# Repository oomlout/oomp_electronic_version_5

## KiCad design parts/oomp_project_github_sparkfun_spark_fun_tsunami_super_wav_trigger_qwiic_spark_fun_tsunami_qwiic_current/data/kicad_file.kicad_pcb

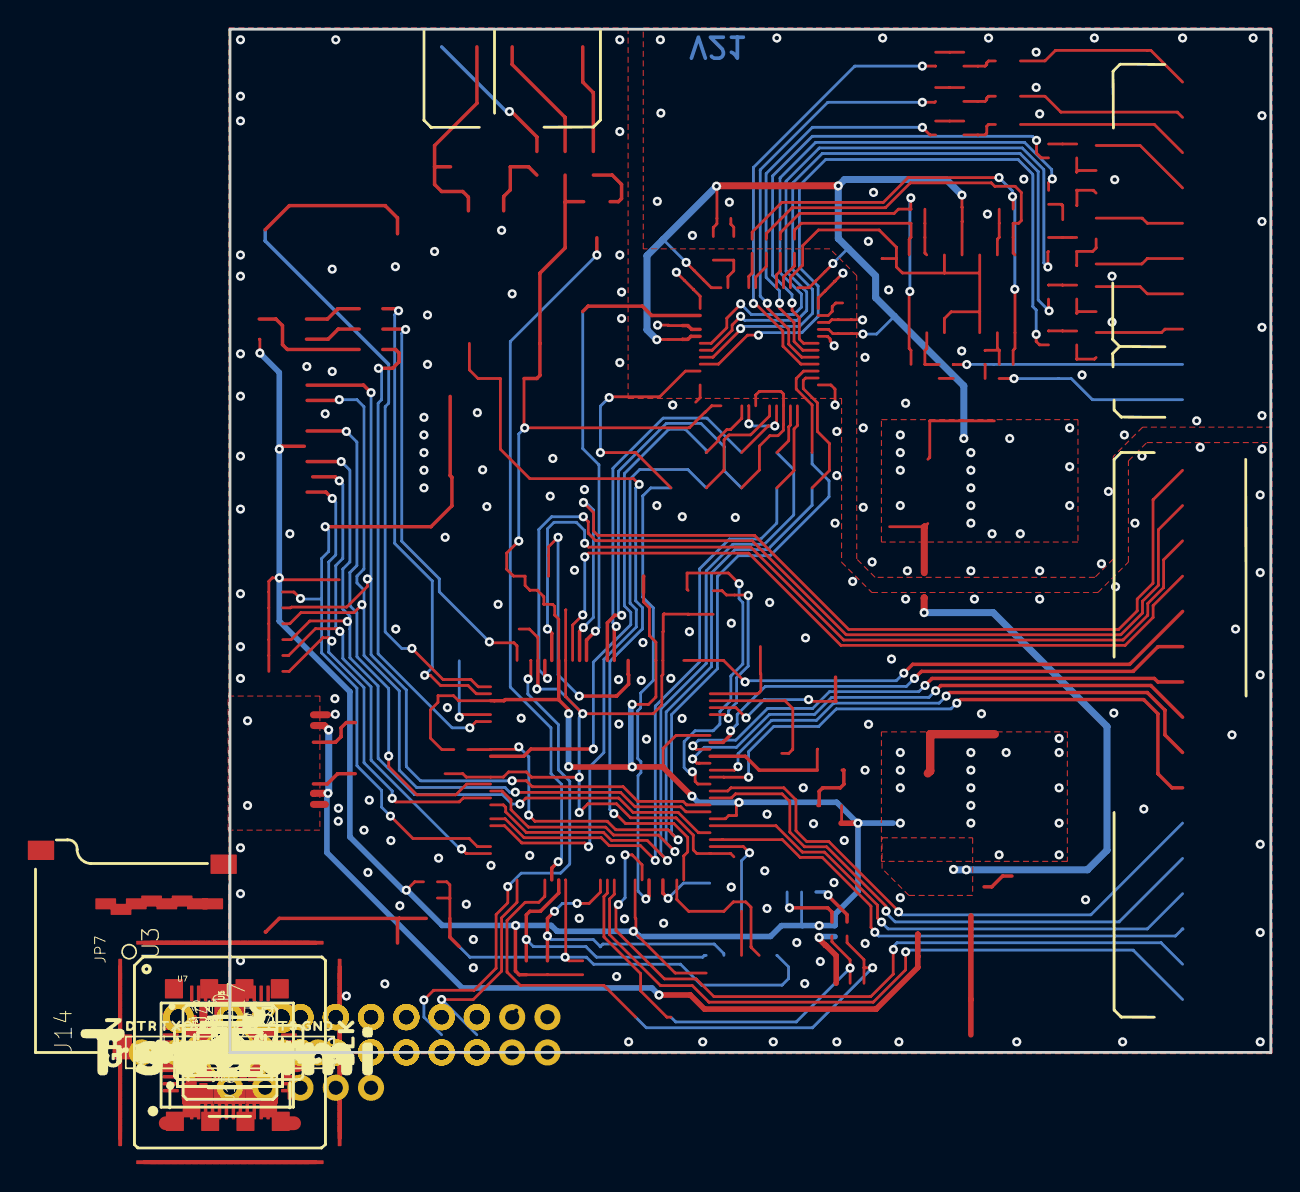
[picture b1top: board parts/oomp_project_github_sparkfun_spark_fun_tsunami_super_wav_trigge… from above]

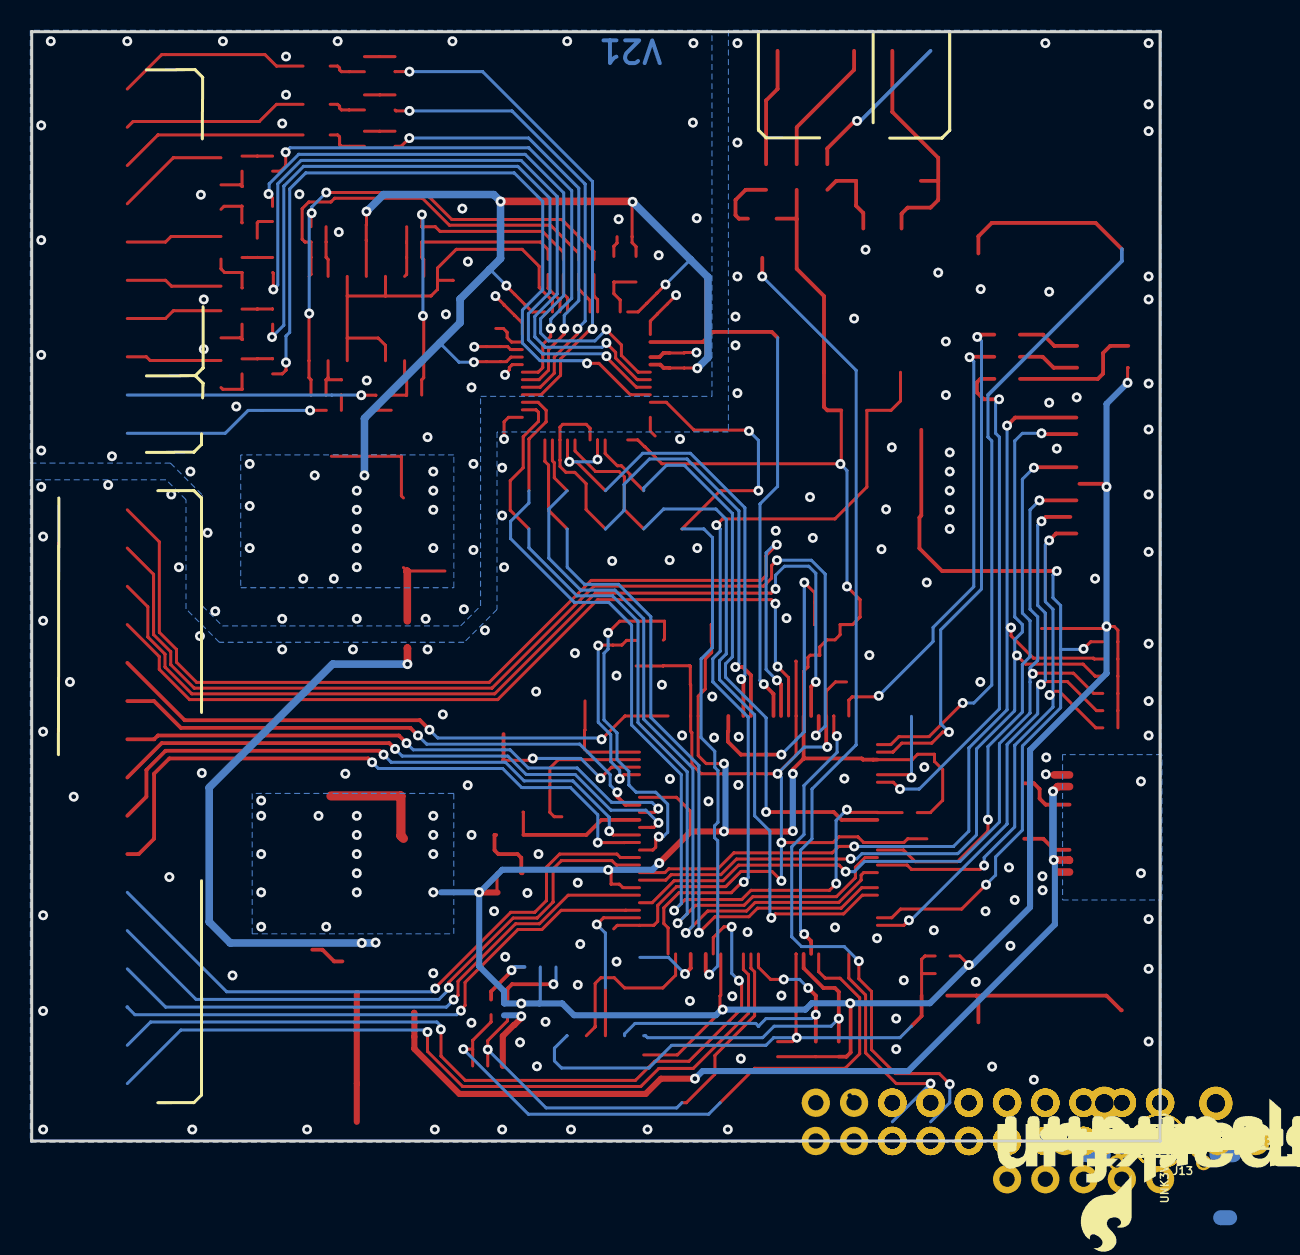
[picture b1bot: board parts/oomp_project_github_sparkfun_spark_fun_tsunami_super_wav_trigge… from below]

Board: 2 copper layers, 74.9 x 73.7 mm, 327 parts (76 on the bottom side), 138 nets.

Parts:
C1: 10nF; 0402-TIGHT
C2, C5, C6, C11, C27: 10uF; 0402-TIGHT
C3, C4, C8, C10, C12, C13, C15, C16, C17, C18, C19, C21, C22, C23, C24, C26, C28, C29, C31, C36, C37, C47, C48, C49, C50, C51, C52, C53, C54, C55, C56, C57, C59, C73, C74, C75, C76, C77, C78, C79, C80: 0.1uF; 0402-TIGHT
C7, C9: 12pF; 0402-TIGHT
C14: 4.7uF; 0402-TIGHT
C20: 10pF; 0603
C25: 2.2uF; 0603
C30, C32, C38, C58, C60, C62, C63, C66, C69, C70, C71, C72: 1.0uF; 0402-TIGHT
C33, C61, C67, C68: 100pF; 0402-TIGHT
C34: 5.6nF; 0603
C35: 390nF; 0603
C39, C40, C41, C42, C43, C44, C45, C46: 22uF; 0805
D1, D3: 1A/40V/500mV; SMA-DIODE
D4: RGB; P-LCC-4-3
FB1, FB2, FB3: 470Ω; 0603
FB4, FB5: 600Ω; 0805
FD1, FD2, FD3, FD4: FIDUCIALUFIDUCIAL; FIDUCIAL-MICRO
FRAME1, FRAME2: FRAME-LEDGER; CREATIVE_COMMONS
H1, H2, H3, H4: STAND-OFF
I2C0: SMT-JUMPER_3_2-NC_TRACE_SILK
J1: VDC-IN; 1X02_NO_SILK
J2: GND-IN; 1X02_NO_SILK
J3: DEBUG; 1X01_NO_SILK
J4: QWIIC; JST04_1MM_RA
J6: 3.3VA; 1X01_NO_SILK
J7: 3.3V; 1X01_NO_SILK
J8: PLAYING; 1X01_NO_SILK
J9: CORTEX_JTAG_DEBUG_PTH_NS; 2X5-PTH-1.27MM-NO_SILK
J10: TRIG2; 2X8_NOSILK
J11: TRIG1; 2X8_NOSILK
J13: 2X5_NOSILK
J14: AUDIO I/O; 2X10_NOSILK
J15: MIDI; 1X05_NO_SILK
J16: USB-C; USB-C-16P-4LAYER-ISOLATED
J17: AGND; 1X01_NO_SILK
J18: 6_PIN_SERIAL_TARGET_SIDE_W_SILK
JP7: USD-SOCKETNEW; MICRO-SD-SOCKET-PP
L1: 10μH; 0805
LOGO2: SFE_LOGO_NAME_FLAME.2_INCH; SFE_LOGO_NAME_FLAME_.2
LOGO3: QWIIC_LOGO_4MM; QWIIC_4MM
Q1: 3.1A/30V/105mΩ; SOT23-3
R1: 33; 0603
R2: 1M; 0603
R3, R4, R18, R23: 10k; 0402-TIGHT
R5: 560Ω; 0402-TIGHT
R6, R9, R10, R19, R20, R21, R22: 100k; 0402-TIGHT
R7, R8: 390; 0603
R11, R12: 240; 0603
R14, R15, R59, R60, R61, R62, R63, R64: 33k; 0402-TIGHT
R16: 2.2; 0603
R17: 5.62k; 0603
R25, R26, R27, R28, R37, R38, R39, R40, R41, R42, R43, R44, R56, R57, R58, R65: 10Ω; 0402-TIGHT
R45, R46, R47, R48, R55: 220; 0603
R49, R50: 5.1k; 0402-TIGHT
R51, R52: 2.2k; 0402-TIGHT
R53, R54: 100; 0603
S1: Reset; TACTILE_SWITCH_SMD_5.2MM
S2, S4: DNP; TACTILE_SWITCH_PTH_RIGHT_ANGLE
S3: User; TACTILE_SWITCH_SMD_5.2MM
TP1: I2C_SCK; TP_15TH
TP2: I2C_SDA; TP_15TH
TP4: MCLK; TP_15TH
TP5: SWDIO/TMS; TP_15TH
TP6: SWCK/TCK; TP_15TH
TP7: TDO; TP_15TH
TP8: TDI; TP_15TH
TP9: NRESET; TP_15TH
U1, U5: LM1117; SOT223
U3: ATSAMS70NXXA-AN; LQFP100
U4: LMV324; SO14
U6: 6N138M; 8-SMD
U7: ADAU1328; LQFP-48
U8: 74AHC1G125W5-7; SOT23-5
U$3: GND_0
U$4, U$73: QWIIC_5MM
U$5: STAT0
U$6: #USER#0
U$7: #RESET#0
U$8, U$9: ROBERTSONICS0
U$10, U$167: #2L#0
U$11: #1L#0
U$12, U$120: #1R#0
U$13: #2R#0
U$14: #3R#0
U$15: #3L#0
U$16: #4L#0
U$17: #4R#0
U$18: #4#3
U$19: #2#5
U$20, U$107: AUDIO_OUT0
U$21, U$46, U$108, U$123: IN0
U$22, U$106: TRIGGER_IN0
U$23, U$85: #GND#0
U$24: #1#0
U$25: SERIAL3
U$26, U$60: SUPER0
U$27, U$99: VIN_5#10_VDC0
U$28, U$84: #AGND#0
U$29: #2#0
U$30: #3#0
U$31, U$56, U$117: #4#0
U$32, U$58, U$118: #5#0
U$33: #6#0
U$34: #7#0
U$35: #8#0
U$36: #9#0
U$37: #10#0
U$38: #11#0
U$39: #12#0
U$40: #PLAYING#30
U$41, U$112: #3V3#0
U$43: #13#0
U$44: #3V3_A#0
U$45, U$122: MIDI0
U$47, U$124: OUT0
U$48: #14#0
U$49: #15#0
U$50: #16#0
U$51: A10
U$52: A20
U$53: A30
U$54: A40
U$55: #5#6
U$57: #2#6
U$59: #4#6
U$61, U$110: #GND#1
U$62, U$68: TRIGGER0
U$63, U$69: TSUNAMI0
U$64, U$70: W0
U$65, U$71: A0
U$66, U$72: V0
U$67, U$111: #VIN#2
U$74: #16#5
U$75: #15#17
U$76: #14#17
U$77: #13#17
U$78: #12#17
U$79: #11#17
U$80: #10#17
U$81: #9#17
U$82: #8#17
U$83: #7#17
U$86: CS17
U$87: BCLK19
U$88: COPI18
U$89: TDMO20
U$91: SPCK22
U$92: TDMI25
U$93: LRCK24
U$94: CIPO23
U$95: APDM26
U$96: #AGND#27
U$97: #AGND#28
U$98: #PLAYING#29
U$102: A117
U$103: A2118
U$104: A32119
U$105: A432120
U$113: #I2C#6
U$116: #1L#3
U$119: #1L#6
U$121: #1R#2
U$141: SFE_LOGO_NAME_FLAME_.1
U$162: #3V3_A#4
U$163: #3V3_QWIIC#0
U$164: #1R#3
U$165: #5#5
U$166: #1L#2
U$168: #2R#3
U$169: #3L#3
U$170: #3R#4
U$171: #4L#4
U$172: #4R#5
U$173: #6#17
U$174: #5#17
U$175: #4#17
U$176: #3#17
U$177: #2#17
U$178: #1#17
UNK3V3_QWIIC0: SMT-JUMPER_2_NO_SILK
Y1: 11.2896 MHz; CRYSTAL-OSC-SMD-5X3

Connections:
3.3V: C6.1, C8.1, C10.1, C11.1, C12.1, C13.1, C15.1, C16.1, C27.1, C28.1, C36.1, C62.1, D4.4, FB3.1, I2C0.2, J7.1, J9.1, JP7.VCC, R3.2, R4.2, R6.2, R9.2, R10.2, R12.2, R16.1, R18.2, R19.2, R20.2, R21.2, R22.2, R23.2, R47.2, R48.2, U1.2, U1.4, U3.5, U3.19, U3.28, U3.68, U3.81, U3.93, U6.8, U7.13, U8.5, UNK3V3_QWIIC0.1
56: D3.C, R45.2, U6.2
ADC1LN: C69.1, U7.40
ADC1LP: C70.1, U7.39
ADC2LN: C71.1, U7.44
ADC2LP: C72.1, U7.43
AGND: C3.2, C5.2, C29.2, C30.2, C31.2, C32.2, C37.2, C38.2, C47.2, C48.2, C49.2, C50.2, C51.2, C52.2, C53.2, C54.2, C55.2, C56.2, C57.2, C58.2, C59.2, C60.2, C73.1, C74.1, C75.1, C76.1, C77.1, C78.1, C79.1, C80.1, FB4.2, J14.2, J14.4, J14.6, J14.8, J14.10, J14.12, J14.14, J14.16, J14.18, J14.20, J17.1, R7.1, U4.11, U7.1, U7.4, U7.32, U7.34, U7.36
AIN1L: C63.2, J14.17
AIN1R: C66.2, J14.19
AOUT1L: C46.1, C47.1, R37.2
AOUT1R: C45.1, C48.1, R38.2
AOUT2L: C44.2, J14.5
AOUT2R: C43.1, C50.1, R40.2
AOUT3L: C42.2, J14.9
AOUT3R: C41.1, C52.1, R42.2
AOUT4L: C40.1, C53.1, R43.2
AOUT4R: C39.1, C54.1, R44.2
APDN: J13.9, U3.70, U7.10
BCLK: J13.6, U3.11, U7.17, U7.21
BLUE_LED: R54.1, U3.31
CC1: J16.A5, R50.2
CC2: J16.B5, R49.2
CM_1.5V: C55.1, U4.3, U4.5, U4.10, U4.12, U7.38
DBUG: J3.1, U3.72
DGND: C1.2, C2.2, C4.2, C6.2, C7.2, C8.2, C9.2, C10.2, C11.2, C12.2, C13.2, C14.2, C15.2, C16.2, C17.2, C18.2, C19.2, C20.2, C21.2, C22.2, C23.2, C24.2, C25.2, C26.2, C27.2, C28.2, C36.2, C62.2, FB4.1, J2.1, J2.2, J4.1, J9.3, J9.5, J9.9, J10.2, J10.4, J10.6, J10.8, J10.10, J10.12, J10.14, J10.16, J11.2, J11.4, J11.6, J11.8, J11.10, J11.12, J11.14, J11.16, J13.10, J15.4, J16.GND, J16.GND2, J18.6, JP7.GND, JP7.GND1, JP7.GND3, R2.1, R8.1, R17.1, R49.1, R50.1, S1.1, S2.1, S3.1, S4.1, U3.3, U3.6, U3.7, U3.8, U3.10, U3.29, U3.67, U6.5, U7.12, U7.25, U8.1, U8.3, Y1.2, Y1.4
GREEN_LED: R53.1, U3.27
I2C_SCK: J4.4, R52.1, TP1.1, U3.55
I2C_SDA: J4.3, R51.1, TP2.1, U3.64
LF: C34.1, C35.1, U7.47
LRCK: J13.5, U3.12, U7.18, U7.22
MCLK: TP4.1, U3.15, U7.2
MIDI-IN-PIN4: J15.1, R45.1
MIDI-IN-PIN5: D3.A, J15.2, U6.3
MIDI-OUT-PIN4: J15.3, R47.1
MIDI-OUT-PIN5: J15.5, R46.2
MIN: R48.1, U3.75, U6.6
MOUT: U3.56, U8.2
unnamed: C7.1, U3.98, Y1.1
unnamed: C9.1, U3.99, Y1.3
unnamed: C19.1, FB1.1, U3.96
unnamed: C14.1, L1.2, U3.90
unnamed: C23.1, FB2.1, U3.86
unnamed: C33.2, C69.2, R14.2, R60.1, U4.8
unnamed: I2C0.3, R51.2
unnamed: J8.1, U3.30
unnamed: I2C0.1, R52.2
unnamed: C34.2, R5.2
unnamed: C63.1, R15.1
unnamed: C61.2, C70.2, R59.2, U4.7
unnamed: C68.2, C72.2, R63.2, U4.1
unnamed: C20.1, R17.2, U3.97
unnamed: C26.1, FB3.2, U3.9
unnamed: C39.2, J14.15
unnamed: C40.2, J14.13
unnamed: C41.2, J14.11
unnamed: C42.1, C51.1, R41.2
unnamed: C43.2, J14.7
unnamed: C75.2, R25.2, R37.1
unnamed: L1.1, R16.2
unnamed: R7.2, R11.1, U5.1
unnamed: R1.1, S1.3, S2.2
unnamed: C74.2, R44.1, R65.2
unnamed: C73.2, R43.1, R58.2
unnamed: R8.2, R12.1, U1.1
unnamed: C80.2, R42.1, R57.2
unnamed: C44.1, C49.1, R39.2
unnamed: C46.2, J14.1
unnamed: C45.2, J14.3
unnamed: J4.2, UNK3V3_QWIIC0.2
unnamed: D4.2, R53.2
unnamed: D4.3, R54.2
unnamed: D4.1, R55.2
unnamed: R46.1, U8.4
unnamed: C3.1, FB5.2, U5.3
unnamed: C56.1, U7.35
unnamed: C61.1, R59.1, R60.2, U4.6
unnamed: C33.1, R14.1, R15.2, U4.9
unnamed: C79.2, R41.1, R56.2
unnamed: C78.2, R28.2, R40.1
unnamed: C76.2, R26.2, R38.1
unnamed: C77.2, R27.2, R39.1
unnamed: C67.2, C71.2, R61.2, R64.1, U4.14
unnamed: C66.1, R62.1
unnamed: C68.1, R63.1, R64.2, U4.2
unnamed: C67.1, R61.1, R62.2, U4.13
unnamed: Q1.1, R2.2
NRESET: C1.1, J9.10, R1.2, R3.1, R10.1, TP9.1, U3.58
OL1: R25.1, U7.28
OL2: R27.1, U7.30
OL3: R56.1, U7.6
OL4: R58.1, U7.8
OR1: R26.1, U7.29
OR2: R28.1, U7.31
OR3: R57.1, U7.7
OR4: R65.1, U7.9
RED_LED: R55.1, U3.25
REGINPUTS: C4.1, D1.C, FB5.1, Q1.2, U1.3
RXD: J18.3, U3.51
SDCD: JP7.CD1, JP7.CD2, R18.1, U3.49
SDCLK: JP7.SCLK, U3.40
SDCMD: JP7.DI, R23.1, U3.79
SDD0: JP7.DO, R21.1, U3.82
SDD1: JP7.RSV2, R22.1, U3.83
SDD2: JP7.RSV1, R19.1, U3.42
SDD3: JP7.CS, R20.1, U3.50
SHIELD: J16.SHLD1, J16.SHLD2, J16.SHLD3, J16.SHLD4, J16.SHLD5, J16.SHLD6, J16.SHLD7, J16.SHLD8
SPI0_CIPO: J13.3, U3.45, U7.24
SPI0_COPI: J13.4, U3.43, U7.23
SPI0_NPCS1: J13.2, R4.1, U3.35, U7.27
SPI0_SPCK: J13.1, U3.41, U7.26
SWCLK/TCK: J9.4, R9.1, TP6.1, U3.63
SWDIO/TMS: J9.2, R6.1, TP5.1, U3.57
TDI: J9.8, TP8.1, U3.74
TDMI: J13.7, U3.46, U7.20
TDMO: J13.8, U3.36, U7.16
TDO: J9.6, TP7.1, U3.77
TXD: J18.2, U3.23
UIA1: J10.7, U3.17
UIA2: J10.5, U3.20
UIA3: J10.3, U3.21
UIA4: J10.1, U3.16
UID1: J11.15, U3.65
UID2: J11.13, U3.69
UID3: J11.11, U3.78
UID4: J11.9, U3.80
UID5: J11.7, U3.84
UID6: J11.5, U3.85
UID7: J11.3, U3.87
UID8: J11.1, U3.88
UID9: J10.15, U3.89
UID10: J10.13, U3.91
UID11: J10.11, U3.92
UID12: J10.9, U3.1
USERSW: S3.3, S4.2, U3.26
VCCA: C5.1, C29.1, C30.1, C31.1, C32.1, C35.2, C37.1, C38.1, C57.1, C58.1, C59.1, C60.1, J6.1, R5.1, R11.2, U4.4, U5.2, U5.4, U7.5, U7.33, U7.37, U7.48
VDDOUT: C17.1, C18.1, C21.1, C22.1, C24.1, C25.1, FB1.2, FB2.2, U3.4, U3.18, U3.22, U3.39, U3.76
VIN: J1.1, J1.2, Q1.3
V_USB: C2.1, D1.A, J16.VBUS1, J16.VBUS2

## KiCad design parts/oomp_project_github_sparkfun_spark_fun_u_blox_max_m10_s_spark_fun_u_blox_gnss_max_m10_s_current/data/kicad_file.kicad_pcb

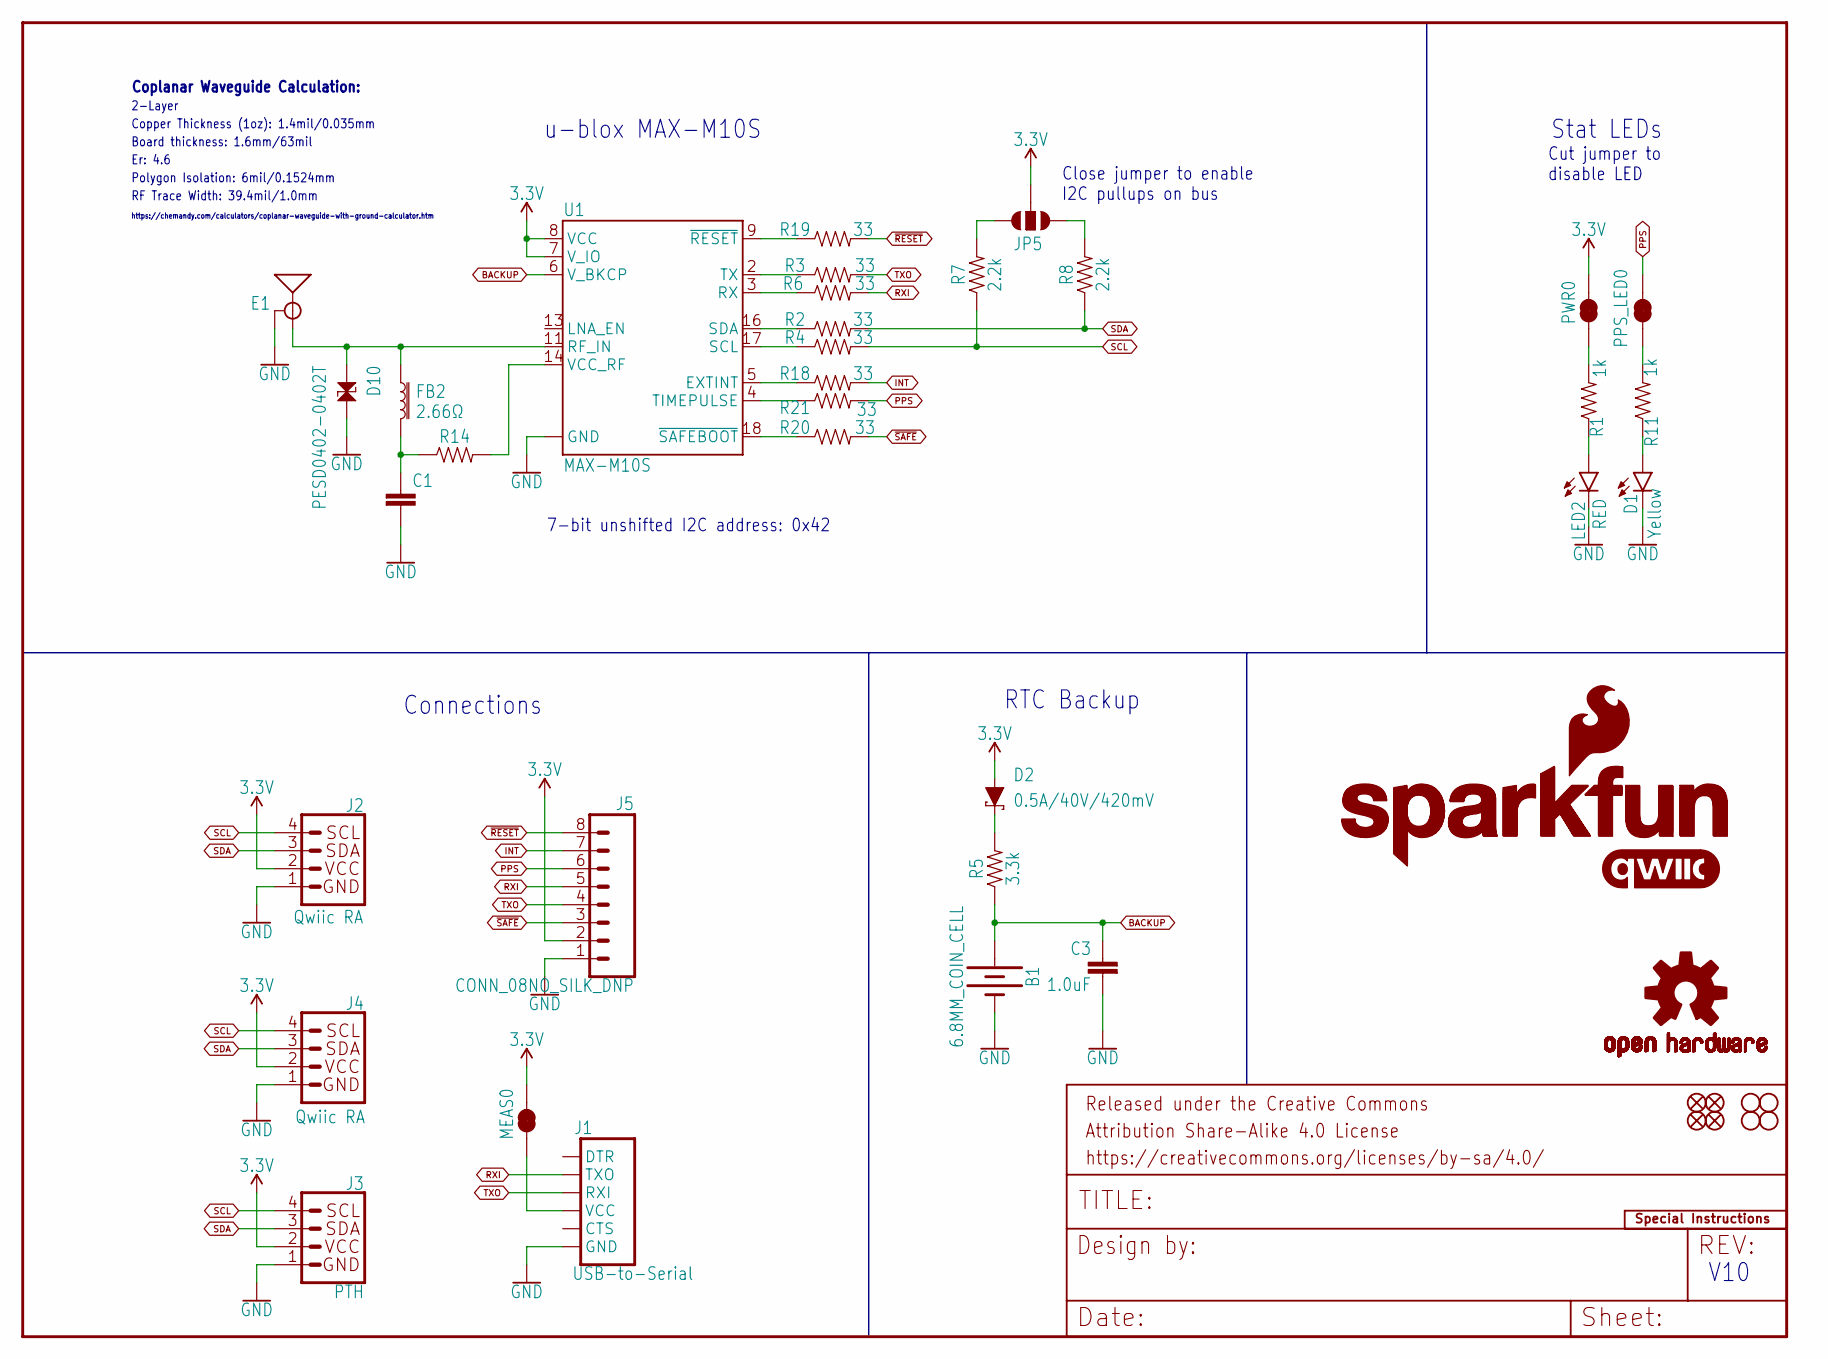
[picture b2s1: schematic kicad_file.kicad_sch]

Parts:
B1: 6.8MM_COIN_CELL; ML414H_IV01E
C1: 47pF; 0402-TIGHT
C3: 1.0uF; 0603
D1: Yellow; LED-0603
D2: 0.5A/40V/420mV; SOD-323
D10: PESD0402-0402T; 0402-TIGHT
E1: ANTENNA-SMA-GROUNDEDEDGE_SMA; SMA-EDGE
FB2: 2.66Ω; 0402-TIGHT
FD1, FD2, FD3, FD4: FIDUCIALUFIDUCIAL; FIDUCIAL-MICRO
FRAME1: FRAME-LETTER; CREATIVE_COMMONS
H1, H2, H3, H4: STAND-OFF
J1: USB-to-Serial; 1X06_NO_SILK
J2, J4: Qwiic RA; JST04_1MM_RA
J3: PTH; 1X04_NO_SILK
J5: CONN_08NO_SILK_DNP; 1X08_NO_SILK
JP5: JUMPER-SMT_3_NO_SILK; SMT-JUMPER_3_NO_SILK
LED2: RED; LED-0603
LOGO1: OSHW-LOGOMINI; OSHW-LOGO-MINI
LOGO2: SFE_LOGO_NAME_FLAME.1_INCH; SFE_LOGO_NAME_FLAME_.1
LOGO3: QWIIC_LOGO_5MM; QWIIC_5MM
LOGO4: SFE_LOGO_NAME.1_INCH; SFE_LOGO_NAME_.1
MEAS0: JUMPER-COMBO_2_NC_TRACE; COMBO-JUMPER_2_NC_TRACE
PPS_LED0: JUMPER-SMT_2_NC_TRACE_SILK; SMT-JUMPER_2_NC_TRACE_SILK
PWR0: JUMPER-SMT_2_NC_TRACE_SILK; SMT-JUMPER_2_NC_TRACE_SILK
R1, R11: 1k; 0603
R2, R3, R4, R6, R18, R19, R20, R21: 33; 0603
R5: 3.3k; 0603
R7, R8: 2.2k; 0603
R14: 33OHM-0402T-1/10W-1%; 0402-TIGHT
U1: MAX-M10S
U$2: SPECIAL_INSTRUCTIONS-ORDERING; ORDERING_INSTRUCTIONS

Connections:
3.3V: D2.A, J2.2, J3.2 (VCC), J4.2, J5.2, JP5.2, MEAS0.2, MEAS0.4 (2), PWR0.2, U1.7 (V_IO), U1.8 (VCC)
ANT_VCC: C1.1, FB2.2, R14.1
BACKUP: B1.+, C3.1, R5.1, U1.6 (V_BKCP)
EXTINT_LV: R18.1, U1.5 (EXTINT)
GND: B1.-, C1.2, C3.2, D1.C, D10.2, E1.GND@0 (GND), E1.GND@1 (GND), E1.GND@2 (GND), E1.GND@3 (GND), J1.6 (GND), J2.1, J3.1 (GND), J4.1, J5.1, LED2.C, U1.1 (GND), U1.10 (GND), U1.12 (GND)
GPS_RF: D10.1, E1.SIG (SIGNAL), FB2.1, U1.11 (RF_IN)
INT: J5.7, R18.2
unnamed: J1.4 (VCC), MEAS0.1, MEAS0.3 (1)
unnamed: D1.A, R11.1
unnamed: PPS_LED0.1, R11.2
unnamed: JP5.1, R8.2
unnamed: D2.C, R5.2
unnamed: JP5.3, R7.2
unnamed: LED2.A, R1.1
unnamed: PWR0.1, R1.2
PPS: J5.6, PPS_LED0.2, R21.2
PPS_LV: R21.1, U1.4 (TIMEPULSE)
RST_LV: R19.1, U1.9 (~RESET)
RXI: J1.3 (TXO), J5.5, R6.2
RXLV: R6.1, U1.3 (RX)
SAFE_LV: R20.1, U1.18 (~SAFEBOOT)
SCL: J2.4, J3.4 (SCL), J4.4, R4.2, R7.1
SCL_LV: R4.1, U1.17 (SCL)
SDA: J2.3, J3.3 (SDA), J4.3, R2.2, R8.1
SDA_LV: R2.1, U1.16 (SDA)
TXLV: R3.1, U1.2 (TX)
TXO: J1.2 (RXI), J5.4, R3.2
VCC_RF: R14.2, U1.14 (VCC_RF)
~RESET: J5.8, R19.2
~SAFE: J5.3, R20.2

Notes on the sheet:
2-Layer
RTC Backup
Cut jumper to disable LED
u-blox MAX-M10S
7-bit unshifted I2C address: 0x42
Polygon Isolation: 6mil/0.1524mm
Board thickness: 1.6mm/63mil
RF Trace Width: 39.4mil/1.0mm
https://chemandy.com/calculators/coplanar-waveguide-with-ground-calculator.htm
Copper Thickness (1oz): 1.4mil/0.035mm
Er: 4.6
V10
Connections
Close jumper to enable I2C pullups on bus
Stat LEDs
Coplanar Waveguide Calculation:

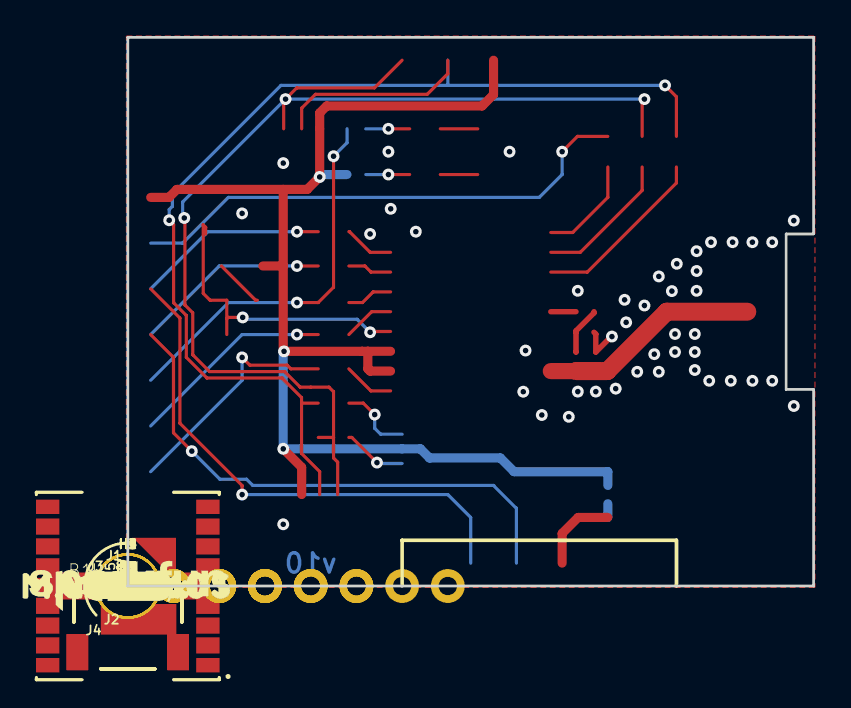
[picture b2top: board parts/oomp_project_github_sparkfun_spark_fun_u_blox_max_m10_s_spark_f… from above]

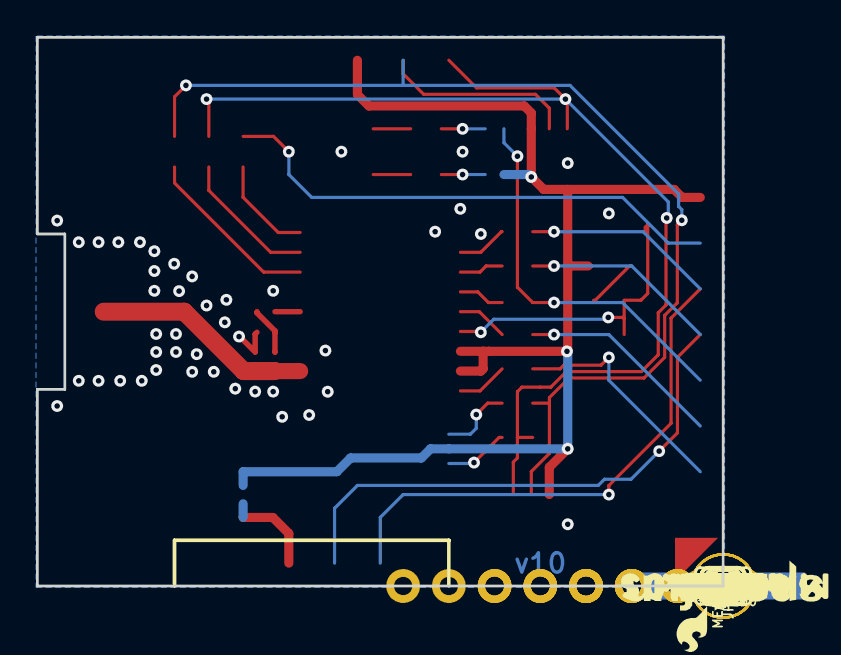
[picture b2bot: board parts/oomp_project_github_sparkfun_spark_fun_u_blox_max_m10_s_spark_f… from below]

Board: 2 copper layers, 38.1 x 30.5 mm, 91 parts (33 on the bottom side), 30 nets.

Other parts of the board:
U$1, U$10, U$26, U$31: #3V3#4
U$3, U$11, U$27, U$34: #GND#5
U$4, U$28: BLK0
U$5, U$29: GRN1
U$6: PPS7
U$7: PWR6
U$8, U$25: #RX#2
U$9, U$22: #TX#3
U$12: ##RST##2
U$13: ##SAFE##0
U$14, U$43: #PPS#1
U$15: #RX#1
U$16: #TX#0
U$18, U$23: MAX#M10S1
U$19, U$37: #0
U$20, U$21: U#BLOX0
U$24: SMA2
U$30: #I�C#0
U$32: #SCL#1
U$33: #SDA#0
U$35: #PPS#0
U$36: #PWR#0
U$38, U$40: #1
U$39: ##RST##0
U$41: #MEAS#0
U$42: #EINT#0
U$44: RX2
U$45: TX3
U$46: #EINT_#0

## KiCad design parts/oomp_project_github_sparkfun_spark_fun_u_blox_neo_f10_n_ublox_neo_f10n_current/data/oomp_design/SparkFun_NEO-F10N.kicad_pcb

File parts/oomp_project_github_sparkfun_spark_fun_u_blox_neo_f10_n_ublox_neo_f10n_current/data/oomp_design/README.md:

# OOMP KiCad design copy

Open `SparkFun_NEO-F10N.kicad_pro` (or the `.kicad_pcb` / `.kicad_sch`) in KiCad. Local OOMP libraries are under `libraries/`. Original inputs are preserved in [../original/](../original/).

Only verified unchanged installed KiCad defaults were renamed. Modified, custom, unmatched and unavailable items remain unchanged. Soldering variants are never swapped during conversion. Existing pad coordinates, nets and UUIDs are preserved.

See [conversion_report.yaml](conversion_report.yaml) for every conversion and skip. Copy this directory before editing; regeneration refuses to overwrite edited design files.

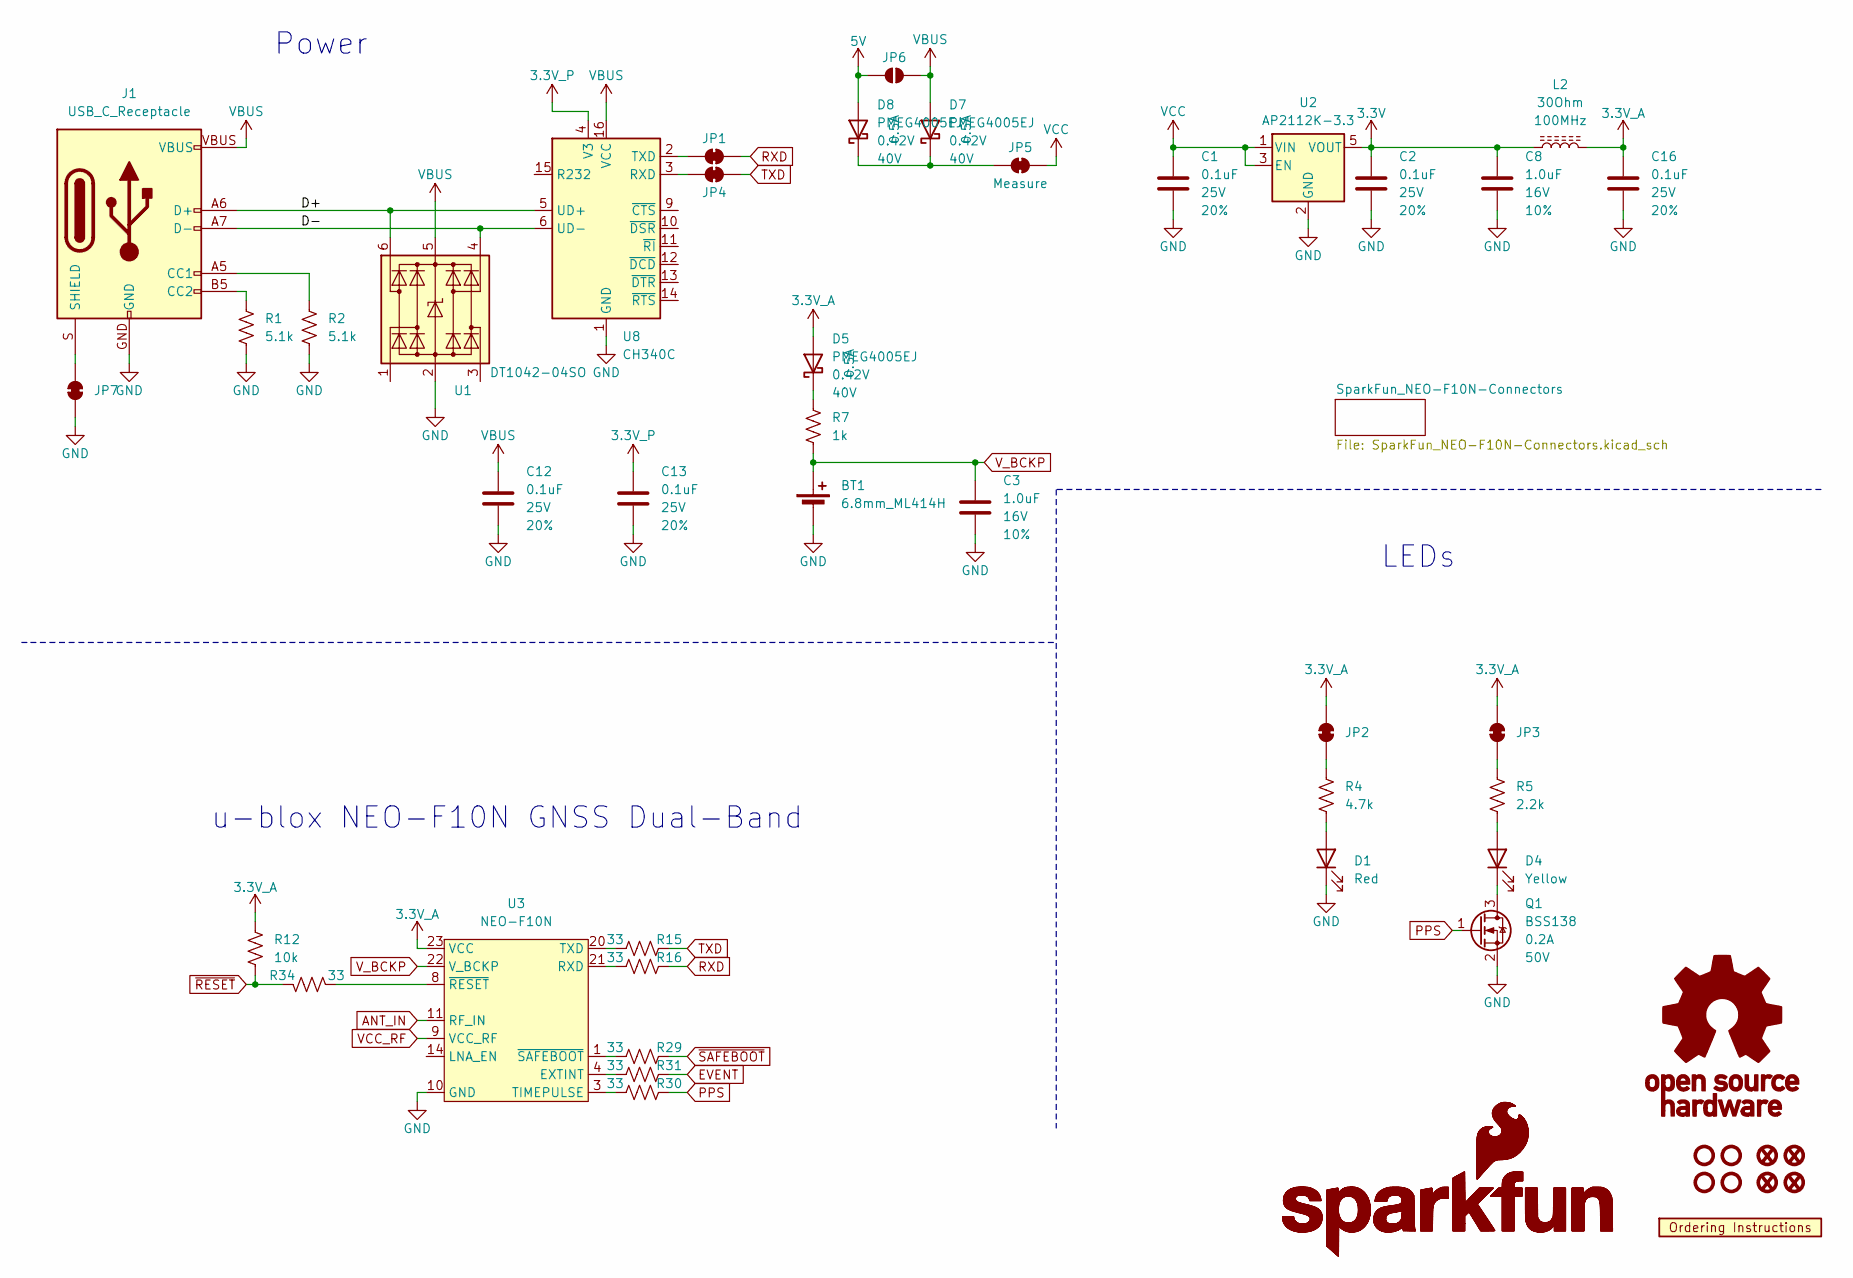
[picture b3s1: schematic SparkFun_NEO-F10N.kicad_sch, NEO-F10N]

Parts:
BT1: 6.8mm_ML414H; ML414H_IV01E
C1, C2, C12, C13, C16: 0.1uF; C_0603_1608Metric; Voltage 25V; Tolerance 20%
C3, C8: 1.0uF; C_0603_1608Metric; Voltage 16V; Tolerance 10%
D1: Red; LED_0603_1608Metric_Red
D4: Yellow; LED_0603_1608Metric_Yellow
D5, D7, D8: PMEG4005EJ; SOD-323
FID1, FID2, FID3, FID4: Fiducial_0.5mm; Fiducial_0.5mm_Mask1mm
G1: OSHW_Logo; Creative_Commons_License
G3, G5: SparkFun_Logo
J1: USB_C_Receptacle; USB-C_16
JP1, JP2, JP3, JP4, JP7: Jumper_2_NC_Trace
JP5: Measure; Jumper_2_PTH_SMD_Combo-NC
JP6: Jumper_2_NO
L2: 30Ohm; C_0603_1608Metric
Q1: BSS138; SOT23-3
R1, R2: 5.1k; R_0603_1608Metric
R4: 4.7k; R_0603_1608Metric
R5: 2.2k; R_0603_1608Metric
R7: 1k; R_0603_1608Metric
R12: 10k; R_0603_1608Metric
R15, R16, R29, R30, R31, R34: 33; R_0603_1608Metric
ST1, ST2, ST3, ST4: Standoff
U1: DT1042-04SO; SOT23-6
U2: AP2112K-3.3; SOT23-5
U3: NEO-F10N; NEO-M9N_M8T_M8U_D9S_F9P_F10N
U7: Ordering_Instructions
U8: CH340C; SO-16

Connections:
3.3V: C2.1, C8.1, L2.1, U2.5 (VOUT); also elsewhere on the board
3.3V_A: C16.1, D5.A, JP2.2 (B), JP3.2 (B), L2.2, R12.1, U3.23 (VCC)
3.3V_P: C13.1, U8.4 (V3)
5V: D8.A, JP6.1 (A); also elsewhere on the board
/D+: J1.A6 (D+), J1.B6 (D+), U1.6 (I/O4), U8.5 (UD+)
/D-: J1.A7 (D-), J1.B7 (D-), U1.4 (I/O3), U8.6 (UD-)
ANT_IN: U3.11 (RF_IN); also elsewhere on the board
EVENT: R31.2; also elsewhere on the board
GND: BT1.-, C1.2, C2.2, C3.2, C8.2, C12.2, C13.2, C16.2, D1.1 (K), J1.GND, JP7.1 (A), Q1.2 (S), R1.2, R2.2, U1.2 (GND), U2.2 (GND), U3.10 (GND), U3.12 (GND), U3.13 (GND), U3.24 (GND), U8.1 (GND); also elsewhere on the board
unnamed: D1.2 (A), R4.2
unnamed: D4.2 (A), R5.2
unnamed: D4.1 (K), Q1.3 (D)
unnamed: D5.C, R7.1
unnamed: J1.A5 (CC1), R2.1
unnamed: J1.B5 (CC2), R1.1
unnamed: J1.S (SHIELD), JP7.2 (B)
unnamed: JP1.1 (A), U8.2 (TXD)
unnamed: JP2.1 (A), R4.1
unnamed: JP3.1 (A), R5.1
unnamed: JP4.1 (A), U8.3 (RXD)
unnamed: D7.C, D8.C, JP5.1 (A)
unnamed: R31.1, U3.4 (EXTINT)
unnamed: R16.1, U3.21 (RXD)
unnamed: R30.1, U3.3 (TIMEPULSE)
unnamed: R15.1, U3.20 (TXD)
unnamed: R34.2, U3.8 (~RESET)
unnamed: R29.1, U3.1 (~SAFEBOOT)
PPS: Q1.1 (G), R30.2; also elsewhere on the board
RXD: JP1.2 (B), R16.2; also elsewhere on the board
TXD: JP4.2 (B), R15.2; also elsewhere on the board
VBUS: C12.1, D7.A, J1.VBUS, JP6.2 (B), U1.5 (VCC), U8.16 (VCC)
VCC: C1.1, JP5.2 (B), U2.1 (VIN), U2.3 (EN)
VCC_RF: U3.9 (VCC_RF); also elsewhere on the board
V_BCKP: BT1.+, C3.1, R7.2, U3.22 (V_BCKP)
~RESET: R12.2, R34.1; also elsewhere on the board
~SAFEBOOT: R29.2; also elsewhere on the board

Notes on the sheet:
LEDs
u-blox NEO-F10N GNSS Dual-Band
Power

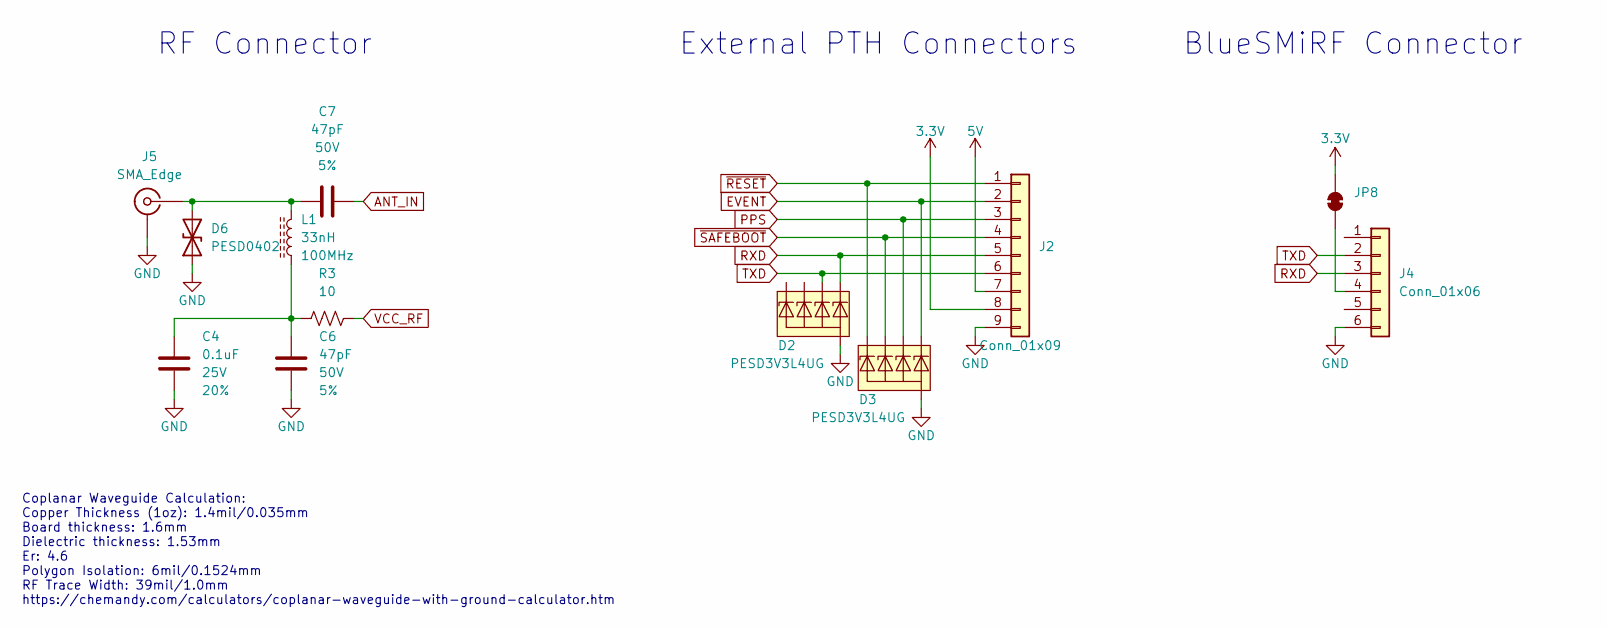
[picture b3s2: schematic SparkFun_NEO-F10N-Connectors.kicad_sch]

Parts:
C4: 0.1uF; C_0603_1608Metric; Voltage 25V; Tolerance 20%
C6, C7: 47pF; C_0603_1608Metric; Voltage 50V; Tolerance 5%
D2, D3: PESD3V3L4UG; SOT-353
D6: PESD0402; C_0402_1005Metric
J2: Conn_01x09; 1x09
J4: Conn_01x06; 1x06
J5: SMA_Edge
JP8: Jumper_2_NC_Trace
L1: 33nH; C_0603_1608Metric
R3: 10; R_0603_1608Metric

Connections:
3.3V: J2.8, JP8.2 (B); also elsewhere on the board
5V: J2.7; also elsewhere on the board
ANT_IN: C7.2; also elsewhere on the board
EVENT: D3.5 (K4), J2.2; also elsewhere on the board
GND: C4.2, C6.2, D2.2 (A), D3.2 (A), D6.1 (A1), J2.9, J4.6, J5.2 (Ext); also elsewhere on the board
unnamed: C4.1, C6.1, L1.1, R3.1
unnamed: C7.1, D6.2 (A2), J5.1 (In), L1.2
unnamed: J4.4, JP8.1 (A)
PPS: D3.4 (K3), J2.3; also elsewhere on the board
RXD: D2.5 (K4), J2.5, J4.3; also elsewhere on the board
TXD: D2.4 (K3), J2.6, J4.2; also elsewhere on the board
VCC_RF: R3.2; also elsewhere on the board
~RESET: D3.1 (K1), J2.1; also elsewhere on the board
~SAFEBOOT: D3.3 (K2), J2.4; also elsewhere on the board

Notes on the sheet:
External PTH Connectors
Coplanar Waveguide Calculation: Copper Thickness (1oz): 1.4mil/0.035mm Board thickness: 1.6mm Dielectric thickness: 1.53mm Er: 4.6 Polygon Isolation: 6mil/0.1524mm RF Trace Width: 39mil/1.0mm https://chemandy.com/calculators/coplanar-waveguide-with-ground-calculator.htm
RF Connector
BlueSMiRF Connector

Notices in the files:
parts/oomp_project_github_sparkfun_spark_fun_tsunami_super_wav_trigger_qwiic_spark_fun_tsunami_qwiic_current/data/original/kicad_file.kicad_sch:
Released under the Creative Commons
https://creativecommons.org/licenses/by-sa/4.0
parts and their libraries:
Released under the Creative Commons Attribution Share-Alike 4.0 License
